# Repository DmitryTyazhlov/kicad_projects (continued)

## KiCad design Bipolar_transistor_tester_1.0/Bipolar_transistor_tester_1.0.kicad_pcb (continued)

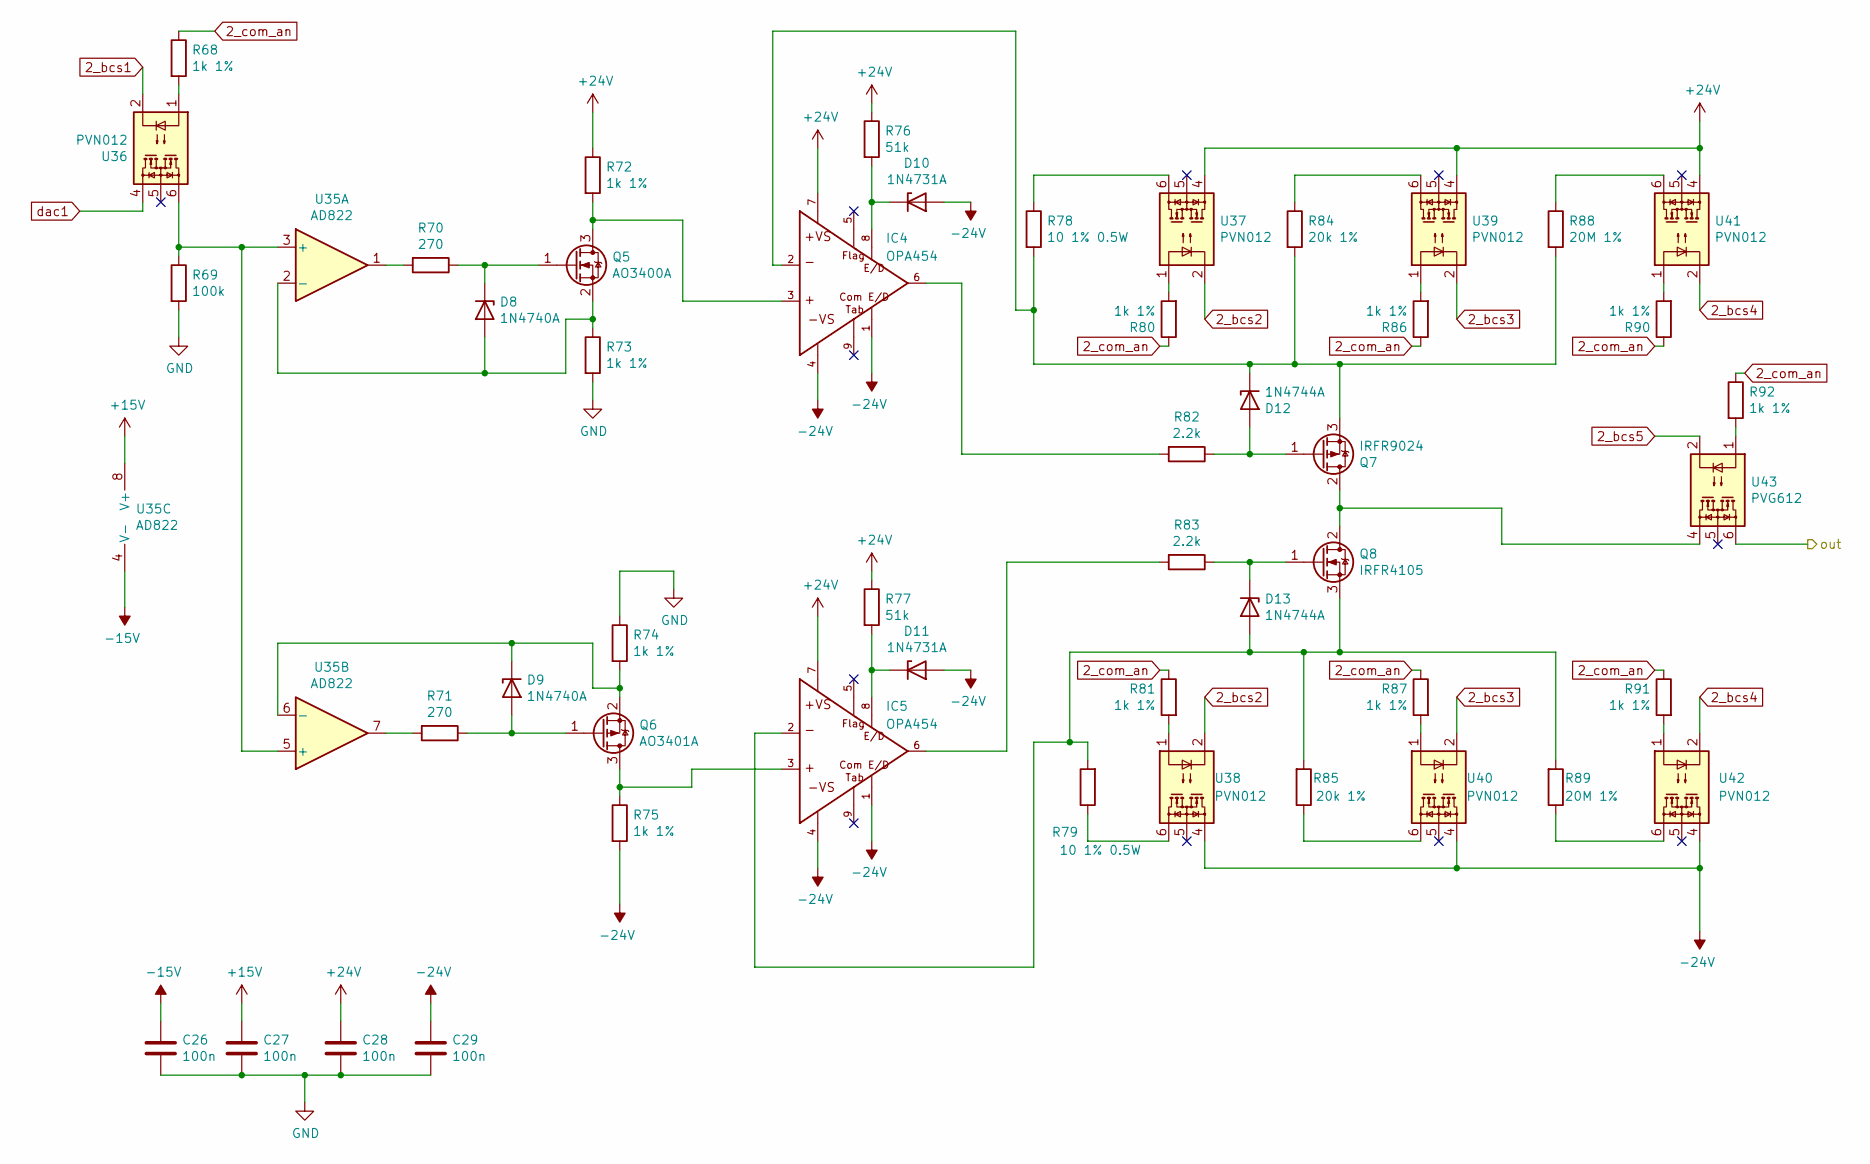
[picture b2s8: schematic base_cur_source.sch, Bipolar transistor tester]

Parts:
C26, C27, C28, C29: 100n; C_0805_2012Metric
D8, D9: 1N4740A; D_DO-41_SOD81_P10.16mm_Horizontal
D10, D11: 1N4731A; D_DO-41_SOD81_P10.16mm_Horizontal
D12, D13: 1N4744A; D_DO-41_SOD81_P10.16mm_Horizontal
IC4, IC5: OPA454; SOIC-8-1EP_3.9x4.9mm_P1.27mm_EP2.29x3mm; PARTNUM 296-22997-5-ND
Q5: AO3400A; SOT-23
Q6: AO3401A; SOT-23
Q7: IRFR9024; TO-252-2
Q8: IRFR4105; TO-252-2
R68, R72, R73, R74, R75, R80, R81, R86, R87, R90, R91, R92: 1k 1%; R_0805_2012Metric
R69: 100k; R_0805_2012Metric
R70, R71: 270; R_0805_2012Metric
R76, R77: 51k; R_0805_2012Metric
R78, R79: 10 1% 0.5W; R_Axial_DIN0309_L9.0mm_D3.2mm_P12.70mm_Horizontal
R82, R83: 2.2k; R_0805_2012Metric
R84, R85: 20k 1%; R_0805_2012Metric
R88, R89: 20M 1%; R_0805_2012Metric
U35: AD822; DIP-8_W7.62mm
U36, U37, U38, U39, U40, U41, U42: PVN012; DIP-6_W7.62mm
U43: PVG612; DIP-6_W7.62mm

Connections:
2_bcs1: U36.2; also elsewhere on the board
2_bcs2: U37.2, U38.2; also elsewhere on the board
2_bcs3: U39.2, U40.2; also elsewhere on the board
2_bcs4: U41.2, U42.2; also elsewhere on the board
2_bcs5: U43.2; also elsewhere on the board
2_com_an: R68.1, R80.1, R81.1, R86.1, R87.1, R90.1, R91.1, R92.1; also elsewhere on the board
+15V: C27.1, U35.8 (V+); also elsewhere on the board
+24V: C28.1, IC4.7, IC5.7, R72.1, R76.1, R77.1, U37.4, U39.4, U41.4; also elsewhere on the board
-15V: C26.1, U35.4 (V-); also elsewhere on the board
-24V: C29.1, D10.2 (A), D11.2 (A), IC4.1, IC4.4, IC5.1, IC5.4, R75.2, U38.4, U40.4, U42.4; also elsewhere on the board
/base_current_meter/in+: U43.6; also elsewhere on the board
GND: C26.2, C27.2, C28.2, C29.2, R69.2, R73.2, R74.1; also elsewhere on the board
unnamed: D8.1 (K), Q5.1 (G), R70.1
unnamed: D8.2 (A), Q5.2 (S), R73.1, U35.2 (-)
unnamed: D9.1 (K), Q6.2 (S), R74.2, U35.6 (-)
unnamed: D9.2 (A), Q6.1 (G), R71.1
unnamed: D10.1 (K), IC4.8, R76.2
unnamed: D11.1 (K), IC5.8, R77.2
unnamed: D12.1 (K), IC4.2, Q7.3 (S), R78.2, R84.2, R88.2
unnamed: D12.2 (A), Q7.1 (G), R82.1
unnamed: D13.1 (K), Q8.1 (G), R83.1
unnamed: D13.2 (A), IC5.2, Q8.3 (S), R79.2, R85.2, R89.2
unnamed: IC4.3, Q5.3 (D), R72.2
unnamed: IC4.6, R82.2
unnamed: IC5.3, Q6.3 (D), R75.1
unnamed: IC5.6, R83.2
unnamed: Q7.2 (D), Q8.2 (D), U43.4
unnamed: R68.2, U36.1
unnamed: R69.1, U35.3 (+), U35.5 (+), U36.6
unnamed: R70.2, U35.1
unnamed: R71.2, U35.7
unnamed: R78.1, U37.6
unnamed: R79.1, U38.6
unnamed: R80.2, U37.1
unnamed: R81.2, U38.1
unnamed: R84.1, U39.6
unnamed: R85.1, U40.6
unnamed: R86.2, U39.1
unnamed: R87.2, U40.1
unnamed: R88.1, U41.6
unnamed: R89.1, U42.6
unnamed: R90.2, U41.1
unnamed: R91.2, U42.1
unnamed: R92.2, U43.1
dac1: U36.4; also elsewhere on the board

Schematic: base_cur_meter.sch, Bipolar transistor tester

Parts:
C30, C31, C32: 100n; C_0805_2012Metric
R93: 10M 1%; R_0805_2012Metric
R94, R96, R97, R98, R100: 1k 1%; R_0805_2012Metric
R95: 100k 1%; R_0805_2012Metric
R99: 5 1% 0.5W; R_Axial_DIN0309_L9.0mm_D3.2mm_P12.70mm_Horizontal
R101: 51k 1%; R_0805_2012Metric
R102: 100; R_0805_2012Metric
U44, U45, U46, U47: PVG612; DIP-6_W7.62mm
U48: INA118; DIP-8_W7.62mm

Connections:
5_bcm1: U44.2; also elsewhere on the board
5_bcm2: U45.2; also elsewhere on the board
5_bcm3: U46.2; also elsewhere on the board
5_bcm4: U47.2; also elsewhere on the board
5_com_an: R94.1, R96.1, R98.1, R100.1; also elsewhere on the board
+15V: C31.1, U48.7 (V+); also elsewhere on the board
-15V: C30.1, U48.4 (V-); also elsewhere on the board
/base_current_meter/in+: R93.2, R95.2, R97.2, R99.2, U48.3 (+); also elsewhere on the board
/base_resistors/in: U44.4, U45.4, U46.4, U47.4, U48.2 (-); also elsewhere on the board
GND: C30.2, C31.2, C32.2, U48.5 (Ref); also elsewhere on the board
unnamed: R93.1, U44.6
unnamed: R94.2, U44.1
unnamed: R95.1, U45.6
unnamed: R96.2, U45.1
unnamed: R97.1, U46.6
unnamed: R98.2, U46.1
unnamed: R99.1, U47.6
unnamed: R100.2, U47.1
unnamed: R101.1, U48.8 (Rg)
unnamed: R101.2, U48.1 (Rg)
unnamed: R102.1, U48.6
adc3: C32.1, R102.2; also elsewhere on the board

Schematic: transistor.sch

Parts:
J25, J26, J27, J28, J29: DJ621-6.3; Knife_Terminal_6.3mm_P5.00mm_Vertical

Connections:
/collector_base_voltage_meter/base_in: J28.1; also elsewhere on the board
/collector_base_voltage_meter/coll_in: J26.1; also elsewhere on the board
/measured transistor/base_supp: J27.1; also elsewhere on the board
/measured transistor/coll_supp: J25.1; also elsewhere on the board
/measured transistor/emitter: J29.1; also elsewhere on the board

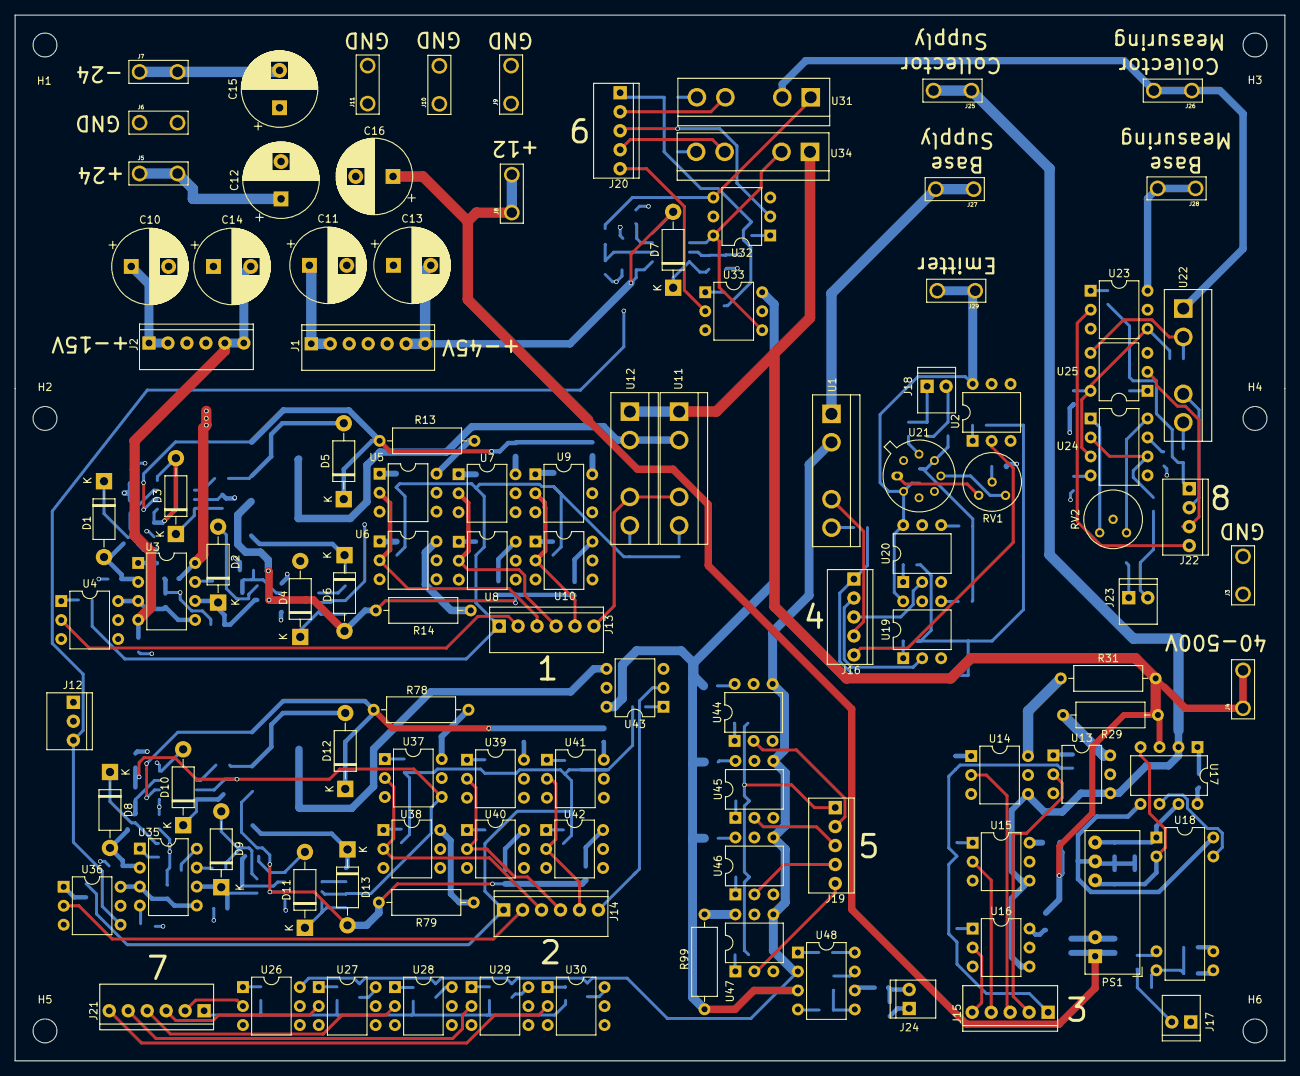
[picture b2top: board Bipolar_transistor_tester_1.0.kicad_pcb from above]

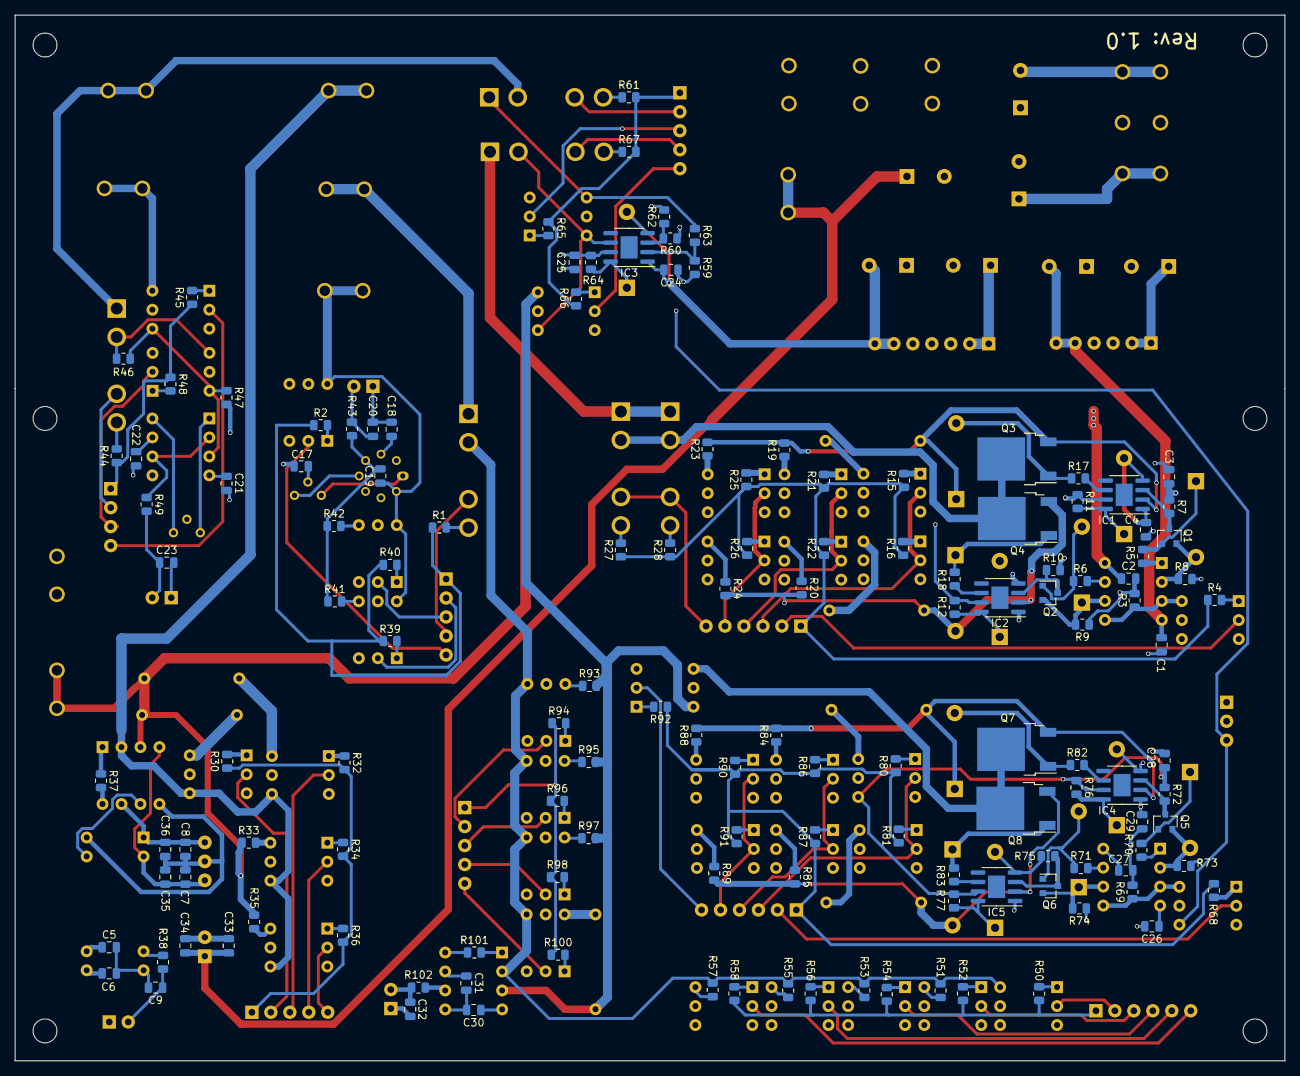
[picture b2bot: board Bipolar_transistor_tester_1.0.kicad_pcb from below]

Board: 4 copper layers, 170.0 x 140.0 mm, 250 parts (137 on the bottom side), 190 nets.

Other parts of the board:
C17, C18, C20: 100n; C_0805_2012Metric
C19: 20p; C_0805_2012Metric
R39, R40, R41: 1k 1%; R_0805_2012Metric
R42: 100M 1%; R_0805_2012Metric
R43: 100; R_0805_2012Metric
RV1: PV32H103; Potentiometer_Bourns_3339H_Vertical
U19, U20: PVN012; DIP-6_W7.62mm
U21: AD549; TO-99-8

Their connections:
4_com_an: R39.2, R40.2; also elsewhere on the board
4_ecm1: U19.2; also elsewhere on the board
4_ecm2: U20.2; also elsewhere on the board
+15V: C18.1, U21.7; also elsewhere on the board
-15V: C17.1, RV1.2, U21.4; also elsewhere on the board
/measured transistor/emitter: C19.1, U19.6, U20.6, U21.2; also elsewhere on the board
GND: C17.2, C18.2, C20.2, U21.3; also elsewhere on the board
unnamed: C19.2, R41.1, R42.1, R43.2, U21.6
unnamed: R39.1, U19.1
unnamed: R40.1, U20.1
unnamed: R41.2, U19.4
unnamed: R42.2, U20.4
unnamed: RV1.1, U21.5
unnamed: RV1.3, U21.1
adc1: C20.1, R43.1; also elsewhere on the board

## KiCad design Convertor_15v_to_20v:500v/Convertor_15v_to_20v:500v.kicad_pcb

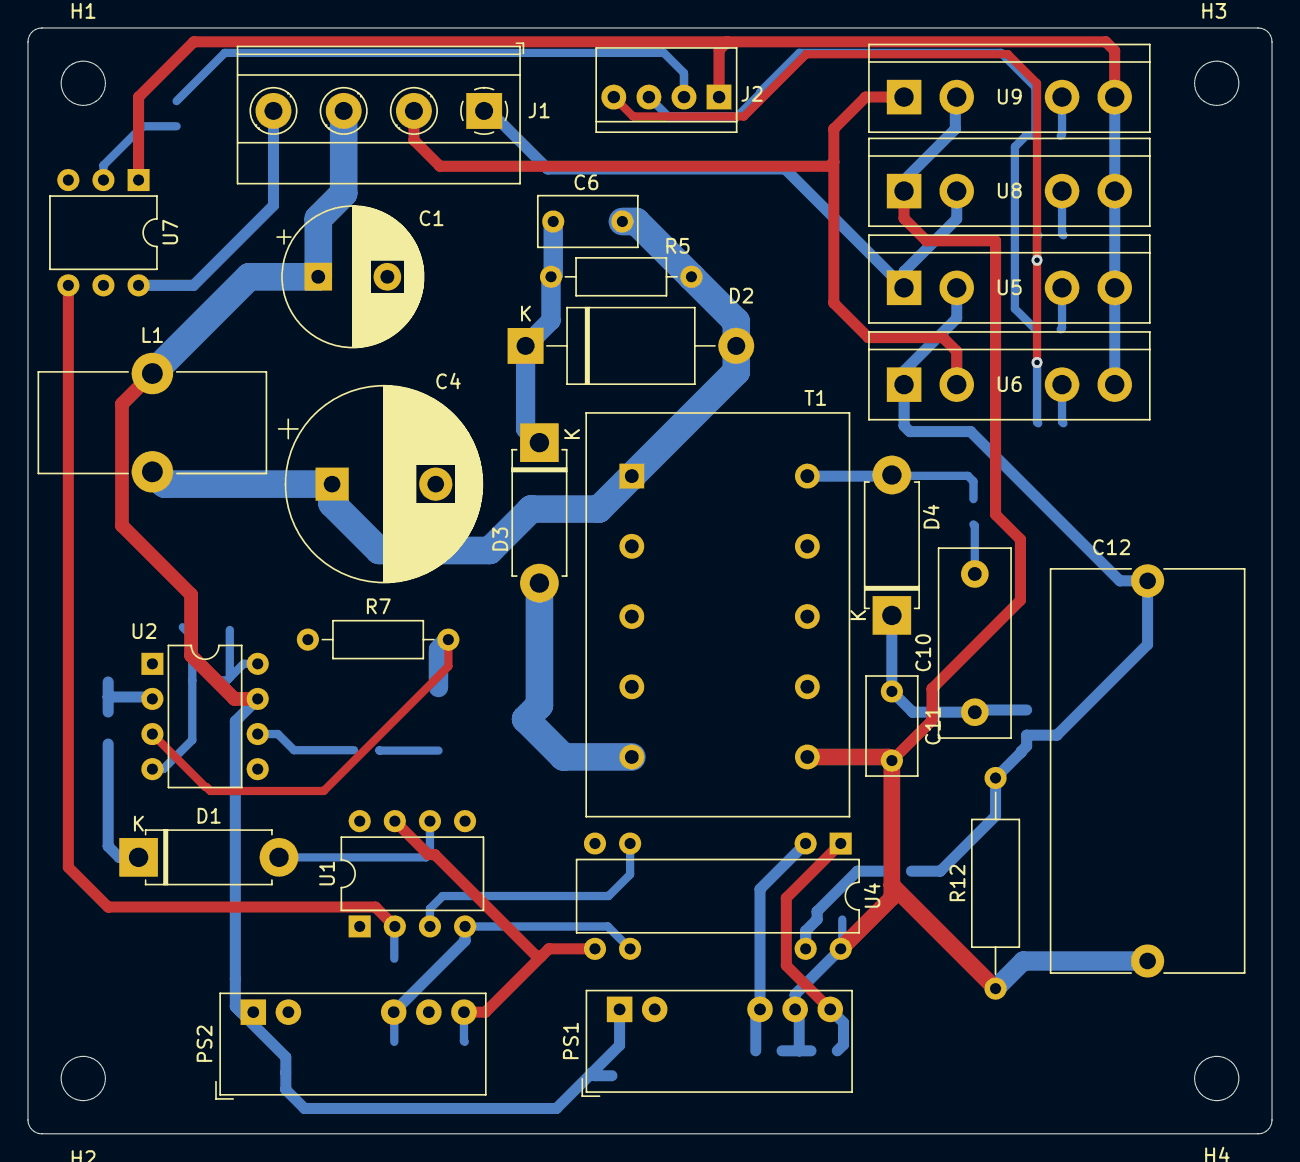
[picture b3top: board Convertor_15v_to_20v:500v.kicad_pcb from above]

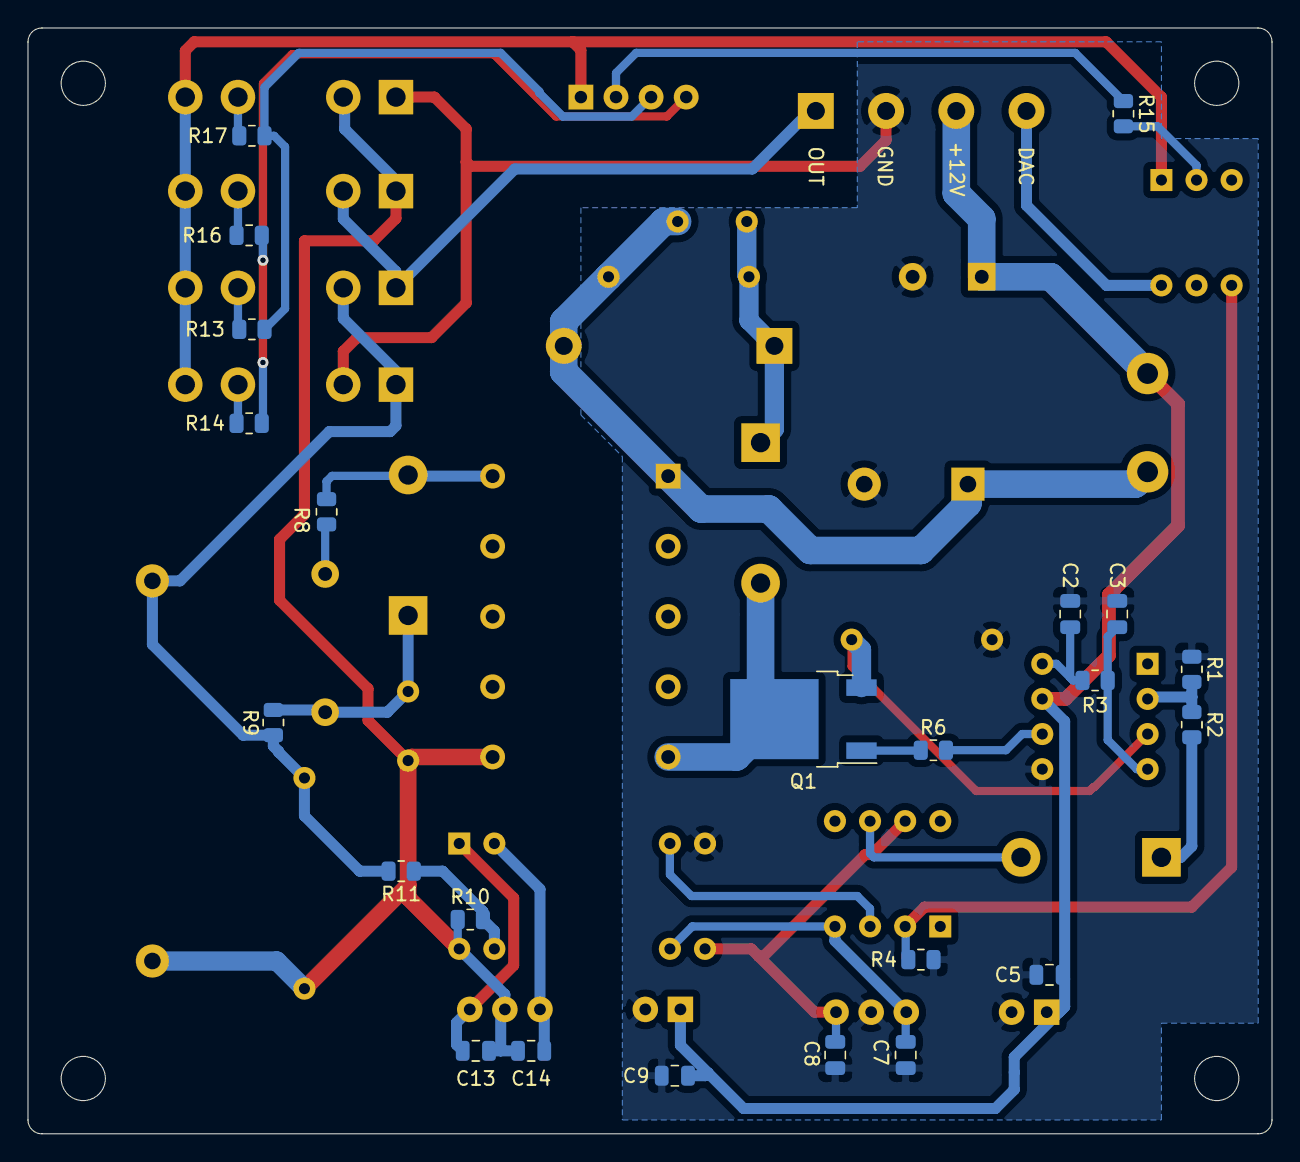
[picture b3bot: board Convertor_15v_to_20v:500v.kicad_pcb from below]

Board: 2 copper layers, 90.0 x 80.0 mm, 54 parts (23 on the bottom side), 36 nets.

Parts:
C1: 220uF 35v; CP_Radial_D10.0mm_P5.00mm
C2: 22nF; C_0805_2012Metric
C3: 2.2nF; C_0805_2012Metric
C4: 2200uF 35v; CP_Radial_D14.0mm_P7.50mm
C5, C7, C8, C9, C13, C14: 1uF; C_0805_2012Metric
C6: 100nF; C_Rect_L7.0mm_W3.5mm_P5.00mm
C10: 8pF 1kV; C_Rect_L13.5mm_W5.0mm_P10.00mm_FKS3_FKP3_MKS4
C11: 1nF 2kV; C_Rect_L7.0mm_W3.5mm_P5.00mm
C12: 2.2uF 630V; C_Rect_L29.0mm_W13.8mm_P27.50mm_MKT
D1, D3, D4: UF4007; D_5W_P10.16mm_Horizontal
D2: 1.5K100A; D_DO-201AE_P15.24mm_Horizontal
H1, H2, H3, H4: MountingHole; MountingHole_3.2mm_M3
J1: Screw_Terminal_01x04; TerminalBlock_Phoenix_MKDS-1,5-4-5.08_1x04_P5.08mm_Horizont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
J2: Conn_01x04_Male; KF2510_4pin
L1: 4uH; L_Toroid_Vertical_L16.3mm_W7.1mm_P7.11mm_Pulse_H
PS1, PS2: TMV1215D; Converter_DCDC_XP_POWER-IHxxxxSH_THT
Q1: IRF640NSTR; TO-252-2
R1, R2: 10k; R_0805_2012Metric
R3: 6.8k; R_0805_2012Metric
R4: 100k; R_0805_2012Metric
R5: 27k; R_Axial_DIN0207_L6.3mm_D2.5mm_P10.16mm_Horizontal
R6: 20; R_0805_2012Metric
R7: 0.2 0.25W; R_Axial_DIN0207_L6.3mm_D2.5mm_P10.16mm_Horizontal
R8, R9, R13, R14, R15, R16, R17: 1k; R_0805_2012Metric
R10: 36k 1%; R_0805_2012Metric
R11: 1.5M 1%; R_0805_2012Metric
R12: 500k 0.5W; R_Axial_DIN0309_L9.0mm_D3.2mm_P15.24mm_Horizontal
T1: Transfomer_1P_1S_custom; EF25 E25.13.7_Vertical
U1: OP177; DIP-8_W7.62mm
U2: UC3845; DIP-8_W7.62mm
U4: ISO124P; DIP-8-16_W7.62mm
U5, U6, U8, U9: CPC1977; i4-PAC
U7: PVN012; DIP-6_W7.62mm

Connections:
+12V: C1.1, C5.1, C9.1, J1.3, L1.1, PS1.1, PS2.1, U2.7
GND: C1.2, C2.2, C3.2, C4.2, C5.2, C7.2, C8.2, C9.2, J1.2, PS1.2, PS2.2, PS2.5, R1.1, R4.1, R7.1, U2.5, U4.4, U6.2, U9.1
GND2: C11.2, C12.2, C13.2, C14.2, PS1.5, R10.1, R12.1, T1.6, U4.8, U8.1, U9.2
HV_output: J1.1, U5.1, U8.2
unnamed: C2.1, R3.2, U2.8
unnamed: C3.1, R3.1, U2.4
unnamed: C4.1, C6.1, D2.2, L1.2, R5.1, T1.1
unnamed: C6.2, D2.1, D3.1, R5.2
unnamed: C7.1, PS2.4, U1.4, U4.6
unnamed: C8.1, PS2.6, U1.7, U4.5
unnamed: C10.1, C11.1, D4.1, R9.2
unnamed: C10.2, R8.1
unnamed: C12.1, R9.1, R11.2, R12.2, U5.2, U6.1
unnamed: C13.1, PS1.6, U4.1
unnamed: C14.1, PS1.4, U4.2
unnamed: D1.1, R2.2
unnamed: D1.2, U1.6
unnamed: D3.2, Q1.2, T1.5
unnamed: D4.2, R8.2, T1.10
unnamed: Q1.1, R6.1
unnamed: Q1.3, R7.2, U2.3
unnamed: R1.2, R2.1, U2.2
unnamed: R6.2, U2.6
unnamed: R13.1, U5.3
unnamed: R14.2, U6.3
unnamed: R15.2, U7.2
unnamed: R16.1, U8.3
unnamed: R17.2, U9.3
unnamed: U1.3, U4.3
common_anode: J2.1, U5.4, U6.4, U7.1, U8.4, U9.4
dac_in: R4.2, U1.2, U7.4
dac_input: J1.4, U7.6
dac_relay: J2.2, R15.1
feedback: R10.2, R11.1, U4.7
set_negativ: J2.4, R14.1, R16.2
set_positive: J2.3, R13.2, R17.1

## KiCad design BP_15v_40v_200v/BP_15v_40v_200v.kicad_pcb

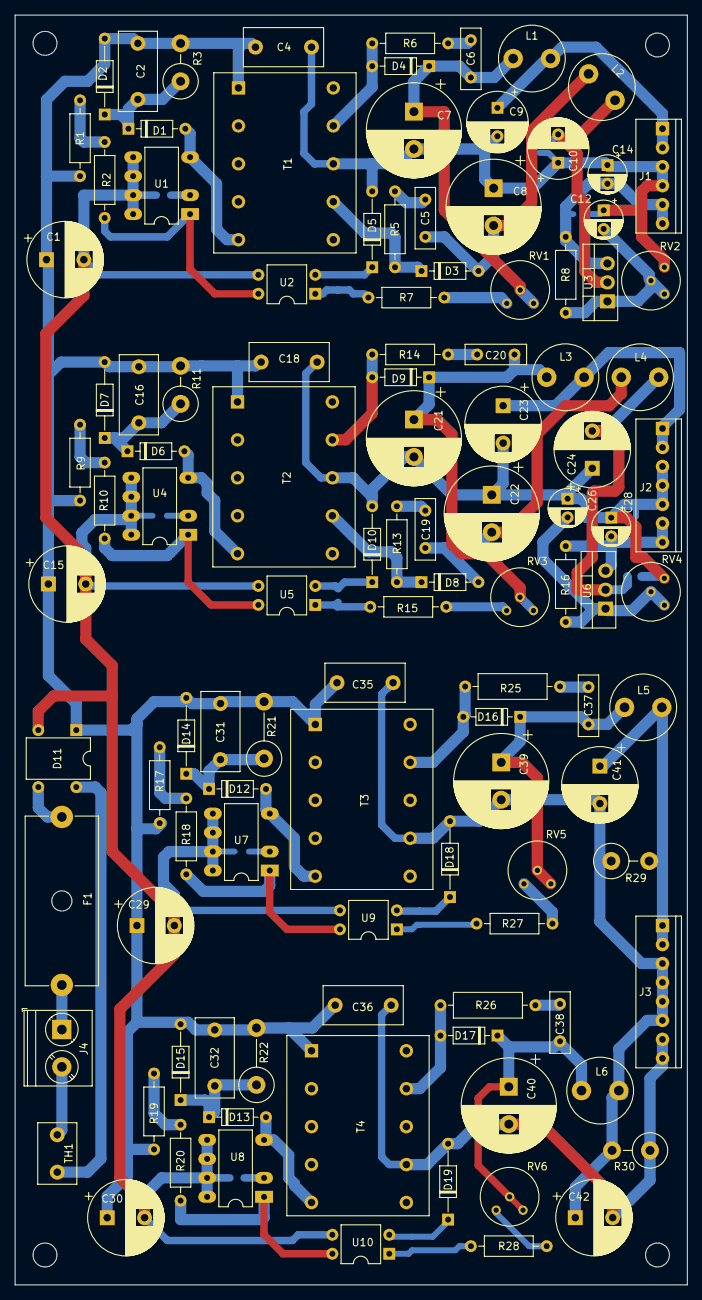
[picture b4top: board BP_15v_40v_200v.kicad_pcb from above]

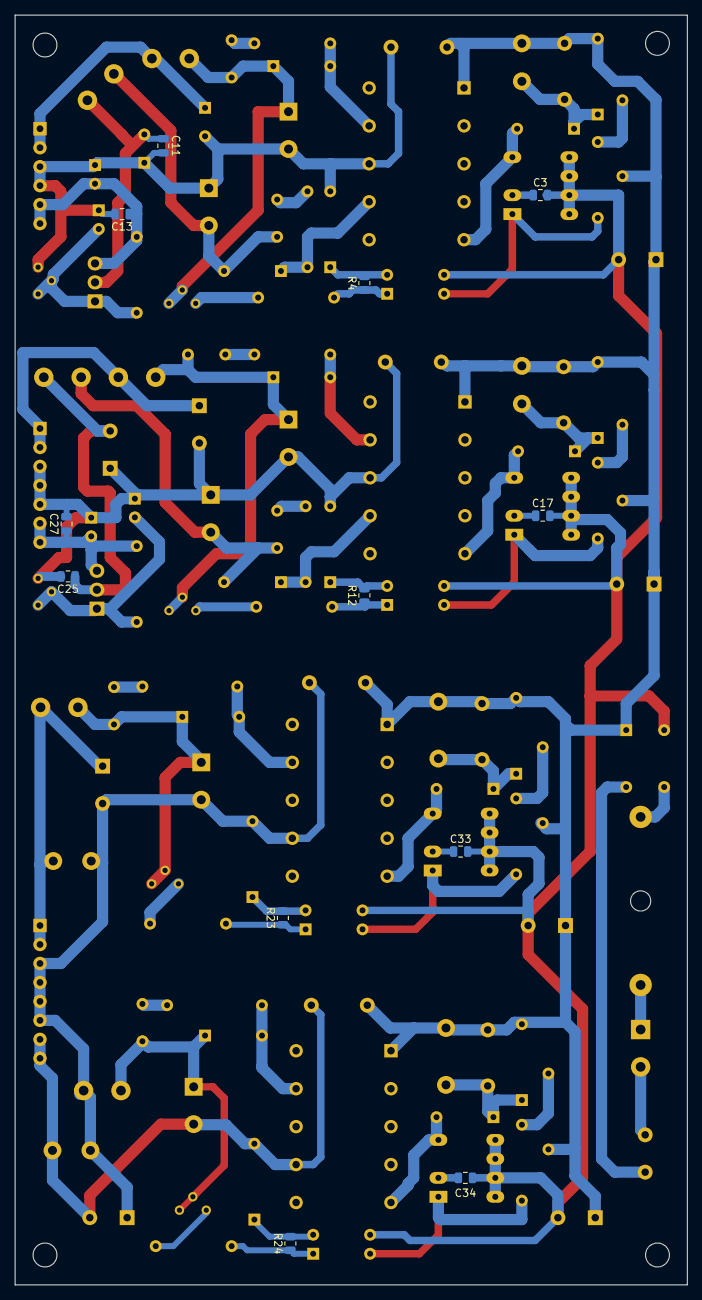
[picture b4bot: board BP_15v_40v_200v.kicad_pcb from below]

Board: 2 copper layers, 90.0 x 170.0 mm, 127 parts (12 on the bottom side), 69 nets.

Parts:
C1, C15, C29, C30: THT 10uF 400v; CP_Radial_D10.0mm_P5.00mm
C2, C16, C31, C32: THT 2.2nF 1kV; C_Disc_D10.5mm_W5.0mm_P7.50mm
C3, C17, C33, C34: SMD 0805 10uF 25V; C_0805_2012Metric
C4, C18, C35, C36: THT CD12-E2GA222MYNS 2.2nF 250V; C_Disc_D10.5mm_W5.0mm_P7.50mm
C5, C6: THT B37979N1820J054 82pF 100v; C_Disc_D8.0mm_W2.5mm_P5.00mm
C7, C8: THT 25v 2200uF; CP_Radial_D12.5mm_P5.00mm
C9, C10: THT 220uF 25V; CP_Radial_D8.0mm_P3.80mm
C11, C13, C25, C27: SMD 100nF 50v; C_0805_2012Metric
C12, C14, C26, C28: THT 10uF 50V; CP_Radial_D5.0mm_P2.50mm
C19, C20: THT ECC-D3A220JGE 22pF 1kV; C_Disc_D8.0mm_W2.5mm_P5.00mm
C21, C22: THT 100v 220uF; CP_Radial_D12.5mm_P5.00mm
C23, C24: THT 100uF 100V; CP_Radial_D10.0mm_P5.00mm
C37, C38: THT ECC-D3A150JGE 15pF 1kV; C_Disc_D8.0mm_W2.5mm_P5.00mm
C39, C40: THT 250v 47uF; CP_Radial_D12.5mm_P5.00mm
C41, C42: THT 250V 10uF; CP_Radial_D10.0mm_P5.00mm
D1, D3, D4, D6, D8, D9, D12, D13, D16, D17: THT UF4007; D_DO-35_SOD27_P7.62mm_Horizontal
D2, D7, D14, D15: THT P6KE180A200B; D_DO-35_SOD27_P10.16mm_Horizontal
D5: THT 1N4737A (Zener 7.5V); D_DO-35_SOD27_P10.16mm_Horizontal
D10: THT 1N4747A (Zener 20V); D_DO-35_SOD27_P10.16mm_Horizontal
D11: DB107; Diode_Bridge_DIP-4_W7.62mm_P5.08mm
D18, D19: THT 1N4764A (Zener 100V); D_DO-35_SOD27_P10.16mm_Horizontal
F1: 1A; Fuseholder_Cylinder-5x20mm_Schurter_0031_8201_Horizontal_Op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
H1, H2, H3, H4: MountingHole; MountingHole_3.2mm_M3_ISO7380
J1: Conn_01x06_KF2510; KF2510_6pin
J2: Conn_01x07_KF2510; KF2510_7pin
J3: Conn_01x08_KF2510; KF2510_8pin
J4: MPW-2 (DS1074-2 M); TerminalBlock_Phoenix_PT-1,5-2-5.0-H_1x02_P5.00mm_Horizontal
L1, L2, L3, L4, L5, L6: THT RL822-3R3K-RC 3,3uH 2,6A; L_Radial_D8.7mm_P5.00mm_Fastron_07HCP
R1, R2, R9, R10, R17, R18, R19, R20: THT 0.25W 4.7M 5%; R_Axial_DIN0207_L6.3mm_D2.5mm_P10.16mm_Horizontal
R3, R11, R29, R30: THT 1W 100k 5%; R_Axial_DIN0414_L11.9mm_D4.5mm_P5.08mm_Vertical
R4, R12, R23, R24: smd 0805 1k 1%; R_0805_2012Metric
R5, R6, R8, R16: THT 0.25W 130 Ohm 5%; R_Axial_DIN0207_L6.3mm_D2.5mm_P10.16mm_Horizontal
R7: THT 0.25W 3.9k 1%; R_Axial_DIN0207_L6.3mm_D2.5mm_P10.16mm_Horizontal
R13, R14: THT 0.25W 470 Ohm 5%; R_Axial_DIN0207_L6.3mm_D2.5mm_P10.16mm_Horizontal
R15: THT 0.25W 9.1k 1%; R_Axial_DIN0207_L6.3mm_D2.5mm_P10.16mm_Horizontal
R21, R22: THT 2W 36k 5%; R_Axial_DIN0414_L11.9mm_D4.5mm_P7.62mm_Vertical
R25, R26: THT 0.5W 680 Ohm 5%; R_Axial_DIN0309_L9.0mm_D3.2mm_P12.70mm_Horizontal
R27, R28: THT 0.25W 47k 1%; R_Axial_DIN0207_L6.3mm_D2.5mm_P10.16mm_Horizontal
RV1, RV2, RV4: 3329H-1-332LF (3.3k); Potentiometer_Bourns_3339H_Vertical
RV3: 3329H-1-103LF (10k); Potentiometer_Bourns_3339H_Vertical
RV5, RV6: 3329H-1-473LF (47k); Potentiometer_Bourns_3339H_Vertical
T1: EF25 E25/13/7 w1-5: 84; w7-8: 15; w8-9: 11; Transformer E25.13.7 (EF25)
T2: EF25 E25/13/7 w1-5: 84; w7-8: 34; w8-9: 29; Transformer E25.13.7 (EF25)
T3, T4: EF25 E25/13/7 w1-5: 84; w7-9: 128; Transformer E25.13.7 (EF25)
TH1: Thermistor JNR08S220L; C_Disc_D8.0mm_W5.0mm_P5.00mm
U1, U4, U7, U8: TNY279P; PowerIntegrations_PDIP-8C
U2, U5, U9, U10: LTV-817; DIP-4_W7.62mm
U3, U6: LM337_TO220; TO-220-3_Vertical

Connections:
220L: F1.1, J4.1
220N: J4.2, TH1.2
+15V: C9.1, J1.1, J1.2, L1.2
+45V: C23.1, J2.1, J2.2, L3.2
+210V: C41.1, J3.1, J3.2, L5.2, R29.2
-15V: C13.1, C14.2, J1.5, J1.6, R8.2, U3.3
-45V: C27.1, C28.2, J2.6, J2.7, R16.2, U6.3
-210V: C36.1, C40.2, C42.2, D19.2, J3.7, J3.8, R30.1, T4.7
GND1: C4.1, C7.2, C8.1, C9.2, C10.1, C11.2, C12.1, C13.2, C14.1, D5.2, J1.3, J1.4, RV2.1, T1.8
GND2: C18.1, C21.2, C22.1, C23.2, C24.1, C25.2, C26.1, C27.2, C28.1, D10.2, J2.3, J2.4, J2.5, RV4.1, T2.8
GND3: C35.1, C39.2, C41.2, C42.1, D18.2, J3.3, J3.4, J3.5, J3.6, L6.2, R29.1, R30.2, T3.7
unnamed: C1.1, C2.1, C4.2, C15.1, C16.1, C18.2, C29.1, C30.1, C31.1, C32.1, C35.2, C36.2, D2.2, D7.2, D11.1, D14.2, D15.2, R1.2, R3.2, R9.2, R11.2, R17.2, R19.2, R21.2, R22.2, T1.1, T2.1, T3.1, T4.1
unnamed: C1.2, C3.2, C15.2, C17.2, C29.2, C30.2, C33.2, C34.2, D11.2, U1.5, U1.6, U1.7, U1.8, U2.3, U4.5, U4.6, U4.7, U4.8, U5.3, U7.5, U7.6, U7.7, U7.8, U8.5, U8.6, U8.7, U8.8, U9.3, U10.3
unnamed: C2.2, D1.1, D2.1, R3.1
unnamed: C3.1, U1.2
unnamed: C5.1, C8.2, D3.2, L2.1
unnamed: C5.2, R5.1
unnamed: C6.1, C7.1, D4.1, L1.1, RV1.1, RV1.2
unnamed: C6.2, R6.1
unnamed: C10.2, C11.1, L2.2, U3.2
unnamed: C12.2, R8.1, RV2.2, RV2.3, U3.1
unnamed: C16.2, D6.1, D7.1, R11.1
unnamed: C17.1, U4.2
unnamed: C19.1, C22.2, D8.2, L4.1
unnamed: C19.2, R13.1
unnamed: C20.1, C21.1, D9.1, L3.1, RV3.1, RV3.2
unnamed: C20.2, R14.1
unnamed: C24.2, C25.1, L4.2, U6.2
unnamed: C26.2, R16.1, RV4.2, RV4.3, U6.1
unnamed: C31.2, D12.1, D14.1, R21.1
unnamed: C32.2, D13.1, D15.1, R22.1
unnamed: C33.1, U7.2
unnamed: C34.1, U8.2
unnamed: C37.1, C39.1, D16.1, L5.1, RV5.1, RV5.2
unnamed: C37.2, R25.1
unnamed: C38.1, C40.1, D17.1, L6.1, RV6.1, RV6.2
unnamed: C38.2, R26.1
unnamed: D1.2, T1.5, U1.4
unnamed: D3.1, R5.2, T1.7
unnamed: D4.2, R6.2, T1.9
unnamed: D5.1, R4.2, U2.2
unnamed: D6.2, T2.5, U4.4
unnamed: D8.1, R13.2, T2.7
unnamed: D9.2, R14.2, T2.9
unnamed: D10.1, R12.2, U5.2
unnamed: D11.3, F1.2
unnamed: D11.4, TH1.1
unnamed: D12.2, T3.5, U7.4
unnamed: D13.2, T4.5, U8.4
unnamed: D16.2, R25.2, T3.9
unnamed: D17.2, R26.2, T4.9
unnamed: D18.1, R23.2, U9.2
unnamed: D19.1, R24.2, U10.2
unnamed: R1.1, R2.2
unnamed: R2.1, U1.1, U2.4
unnamed: R4.1, R7.2, U2.1
unnamed: R7.1, RV1.3
unnamed: R10.1, U4.1, U5.4
unnamed: R9.1, R10.2
unnamed: R12.1, R15.2, U5.1
unnamed: R15.1, RV3.3
unnamed: R17.1, R18.2
unnamed: R18.1, U7.1, U9.4
unnamed: R19.1, R20.2
unnamed: R20.1, U8.1, U10.4
unnamed: R23.1, R27.2, U9.1
unnamed: R24.1, R28.2, U10.1
unnamed: R27.1, RV5.3
unnamed: R28.1, RV6.3

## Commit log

2022-03-14 add project
2022-04-01 converter up scheme, pcb done
2022-04-22 tester up
2022-05-12 bipolar tester is done
2022-05-12 bipolar tester add connectors numbers
2022-05-12 create amplifier logic signal
2022-05-15 add old_convertor
2022-05-15 old_convertor done
2022-05-15 add gitignore
2022-05-15 add list components
2022-05-15 Convertor edit dcp011515 to tmv1215d
2022-05-15 edit name gitignore
2022-05-15 remove .gitigore
2022-06-22 edit resistors cpc1977
2022-06-22 edit resitors cpc1977
